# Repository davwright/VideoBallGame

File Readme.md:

# Video Ball Game
A faithful reproduction of  May 1976 ["Video Ball Game"](https://archive.org/details/EA1976/EA%201976-05%20May/page/n39/mode/2up) by [Electronics Australia](https://en.wikipedia.org/wiki/Electronics_Australia) magazine.  
Thanks to the kind help of [Jon Stanley](https://www.electronixandmore.com/projects/pong/index.html), who also built this. John's [demo](https://vimeo.com/801468536).  

The files are [kicad](https://www.kicad.org/) schematics and PCB.

# Fixes
The [errata](https://archive.org/details/EA1976/EA%201976-07%20July/page/n125/mode/2up) in July 1976 on page 125 list a few corrections.
* IC 5 is incorrectly shown as NAND on the schematic. Jon also discovered this independently.
* 2 0.0047uF polystyrene.
* There is also an error in a the RF circuit, but we are not building that.
* The Quad NAND and NOR integrated circuits today have diffirent pin configurations than those in 1976. This means the circuit board as is cannot be used.

# Improvements
* The 2200uF Capacitor is replaced with a 0.33uF capacitor and a 7806 6V regulator, that converts the 9V battery down to a stable 6V.
* 0.1uF decoupling capacitors are added to the VCC pins.
* pin headers are made for all switches and connectors so that they are all on one side of the board.
* ground and probe pins are added across the circuit for debugging.
* the board is printed double-sided, with a ground back plate, and removing the need for any jumper wires.
* the RF tuner circuit is completely removed, and the video signal is directly fed to composite video.
* Replaced IC5 with NOR. it is incorrectly NAND on schematic. This changes a lot.

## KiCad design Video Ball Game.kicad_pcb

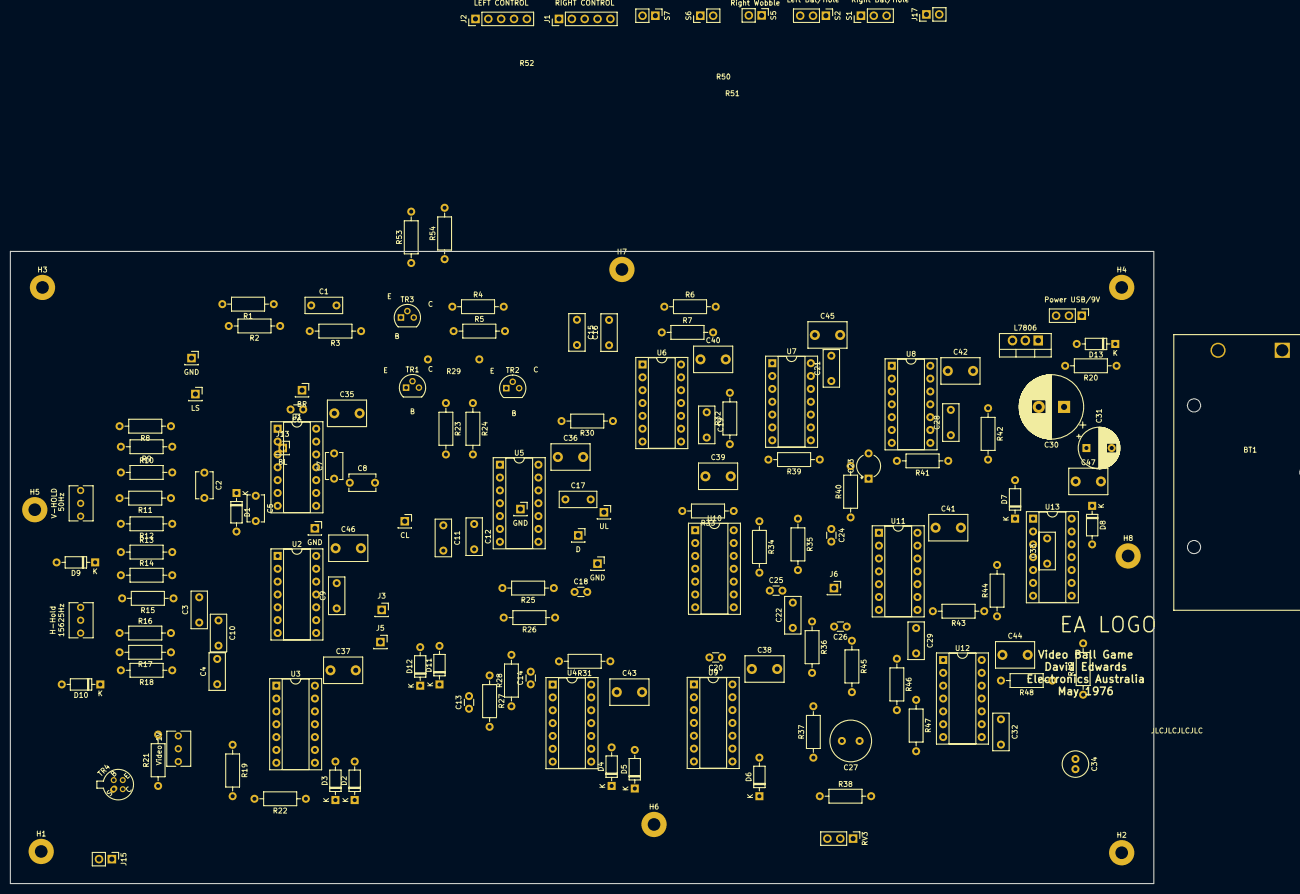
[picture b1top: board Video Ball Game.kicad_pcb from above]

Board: 2 copper layers, 226.1 x 125.0 mm, 168 parts (1 on the bottom side), 112 nets, no tracks yet.

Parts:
BT1: 9V; BatteryHolder_Eagle_12BH611-GR
C1, C3, C4, C9, C10, C19, C21, C28, C29, C32: 10nF red; C_Rect_L7.2mm_W3.0mm_P5.00mm_FKS2_FKP2_MKS2_MKP2
C2, C5, C7, C8: 330pF blue; C_Disc_D5.1mm_W3.2mm_P5.00mm
C6, C13, C14, C18, C24: 100pF blue; C_Disc_D3.0mm_W1.6mm_P2.50mm
C11, C12: 4.7nF red; C_Rect_L7.2mm_W3.0mm_P5.00mm_FKS2_FKP2_MKS2_MKP2
C15, C16, C33: 100nF red; C_Rect_L7.2mm_W3.0mm_P5.00mm_FKS2_FKP2_MKS2_MKP2
C17, C22: 33nF red; C_Rect_L7.2mm_W3.0mm_P5.00mm_FKS2_FKP2_MKS2_MKP2
C20: 220pF blue; C_Disc_D3.0mm_W1.6mm_P2.50mm
C23: 1uF TANTALUM; CP_Radial_Tantal_D4.5mm_P5.00mm
C25, C26: 330pF blue; C_Disc_D3.0mm_W1.6mm_P2.50mm
C27: 220uF elec 16VW 8x11 mm P 3.5; C_Radial_D8.0mm_H11.5mm_P3.50mm
C30: 2200uF elec; CP_Radial_D12.5mm_P5.00mm
C31: 22uF elec 16VW; CP_Radial_D8.0mm_P5.00mm
C34: 47uF elec 16VW radial 5x11mm P2.0; C_Radial_D5.0mm_H11.0mm_P2.00mm
C35, C36, C37, C38, C39, C40, C41, C42, C43, C44, C45, C46, C47: 100nF bypass red; C_Disc_D7.5mm_W5.0mm_P5.00mm
D1, D2, D3, D4, D5, D6, D7, D8, D9, D10, D11, D12, D13: 1N4148; D_DO-35_SOD27_P7.62mm_Horizontal
H1, H2, H3, H4, H5, H6, H7, H8: MountingHole; MountingHole_2.5mm_Pad
J1: RIGHT CONTROL; PinHeader_1x05_P2.54mm_Vertical
J2: LEFT CONTROL; PinHeader_1x05_P2.54mm_Vertical
J3: FS; PinSocket_1x01_P2.54mm_Vertical
J4: UL; PinSocket_1x01_P2.54mm_Vertical
J5: NH; PinSocket_1x01_P2.54mm_Vertical
J6: LL; PinSocket_1x01_P2.54mm_Vertical
J7, J9, J10, J11: GND; PinSocket_1x01_P2.54mm_Vertical
J8: LS; PinSocket_1x01_P2.54mm_Vertical
J12: D; PinSocket_1x01_P2.54mm_Vertical
J13: BL; PinSocket_1x01_P2.54mm_Vertical
J14: CL; PinSocket_1x01_P2.54mm_Vertical
J15: Video; PinHeader_1x02_P2.54mm_Vertical
J16: BR; PinSocket_1x01_P2.54mm_Vertical
J17: USB_B_Micro; PinHeader_1x02_P2.54mm_Vertical
R1: 390k; R_Axial_DIN0207_L6.3mm_D2.5mm_P10.16mm_Horizontal
R2, R14, R27, R28, R31: 22k; R_Axial_DIN0207_L6.3mm_D2.5mm_P10.16mm_Horizontal
R3: 2.2k; R_Axial_DIN0207_L6.3mm_D2.5mm_P10.16mm_Horizontal
R4, R5, R6, R7, R42, R46, R47: 470k; R_Axial_DIN0207_L6.3mm_D2.5mm_P10.16mm_Horizontal
R8, R9, R19, R21, R33, R34, R35, R40, R49, R53, R54: 10k; R_Axial_DIN0207_L6.3mm_D2.5mm_P10.16mm_Horizontal
R10, R11, R15: 33k; R_Axial_DIN0207_L6.3mm_D2.5mm_P10.16mm_Horizontal
R12: 56k; R_Axial_DIN0207_L6.3mm_D2.5mm_P10.16mm_Horizontal
R13, R23, R24, R32, R43: 47k; R_Axial_DIN0207_L6.3mm_D2.5mm_P10.16mm_Horizontal
R16: 330k; R_Axial_DIN0207_L6.3mm_D2.5mm_P10.16mm_Horizontal
R17: 1.2M; R_Axial_DIN0207_L6.3mm_D2.5mm_P10.16mm_Horizontal
R18, R36: 220k; R_Axial_DIN0207_L6.3mm_D2.5mm_P10.16mm_Horizontal
R20, R22, R37: 1k; R_Axial_DIN0207_L6.3mm_D2.5mm_P10.16mm_Horizontal
R25, R26, R29, R30, R44, R48: 10M; R_Axial_DIN0207_L6.3mm_D2.5mm_P10.16mm_Horizontal
R38: 3.3k; R_Axial_DIN0207_L6.3mm_D2.5mm_P10.16mm_Horizontal
R39, R41: 150k; R_Axial_DIN0207_L6.3mm_D2.5mm_P10.16mm_Horizontal
R45: 2.2M; R_Axial_DIN0207_L6.3mm_D2.5mm_P10.16mm_Horizontal
R50, R51: 22k; no pads
R52: 10k; no pads
RV1, RV2, RV4: 4.7k; Potentiometer_Bourns_3266Y_Vertical
RV3: 100k linear speed; PinHeader_1x03_P2.54mm_Vertical
S1: Right Bat/Hole; PinHeader_1x03_P2.54mm_Vertical
S2: Left Bat/Hole; PinHeader_1x03_P2.54mm_Vertical
S3: Power USB/9V; PinHeader_1x03_P2.54mm_Vertical
S5: Right Wobble; PinHeader_1x02_P2.54mm_Vertical
S6: Left Wobble; PinHeader_1x02_P2.54mm_Vertical
S7: Interaction; PinHeader_1x02_P2.54mm_Vertical
TR1, TR2: Q_NPN_BCE; TO-92
TR3: BC558; TO-92
TR4: Q_NPN_BCES; TO-72-4
U1, U2, U3, U4, U9, U10: 4011 QUAD NAND; DIP-14_W7.62mm_Socket
U5, U6, U7, U8, U11, U12, U13: 4001 QUAD NOR; DIP-14_W7.62mm_Socket
U14: L7806; TO-220-3_Vertical

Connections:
+6V: C31.1, C35.1, C36.1, C37.1, C38.1, C39.1, C40.1, C41.1, C42.1, C43.1, C44.1, C45.1, C46.1, C47.1, J1.4, J2.4, R8.1, R9.1, R19.1, R25.1, R26.1, R27.1, R28.1, R31.1, R33.1, R34.1, R35.1, R36.1, R53.2, R54.2, TR3.3 (E), U1.14 (VDD), U2.14 (VDD), U3.14 (VDD), U4.14 (VDD), U5.14 (VDD), U6.14 (VDD), U7.14 (VDD), U8.14 (VDD), U9.14 (VDD), U10.14 (VDD), U11.14 (VDD), U12.14 (VDD), U13.14 (VDD), U14.3 (OUT)
A: S1.2 (B), U4.2
B: S2.2 (B), U4.6
BL: C7.1, C14.2, J13.1, U1.5, U1.10, U9.1
BR: C6.1, C13.2, J16.1, U1.13, U3.3
BX: RV3.3, U5.10, U5.13
C: U4.9, U11.10, U13.5, U13.8
CL: C8.1, C18.2, J14.1, U1.8, U1.11, U9.2
D: U4.8, U11.11
E: U9.8, U9.9, U9.11
Earth: BT1.2 (-), C11.2, C12.2, C23.2, C26.1, C27.2, C30.2, C31.2, C34.2, C35.2, C36.2, C37.2, C38.2, C39.2, C40.2, C41.2, C42.2, C43.2, C44.2, C45.2, C46.2, C47.2, D13.2 (A), H1.1, H2.1, H3.1, H4.1, H5.1, H6.1, H7.1, H8.1, J1.1, J1.2, J2.1, J2.2, J7.1, J9.1, J10.1, J11.1, J15.2, R1.2, R2.2, R39.2, R40.2, R41.2, R43.2, RV1.3, RV2.3, RV4.3, TR4.3 (E), TR4.4 (S), U1.7 (VSS), U2.7 (VSS), U3.7 (VSS), U4.7 (VSS), U5.7 (VSS), U6.7 (VSS), U7.7 (VSS), U8.7 (VSS), U9.7 (VSS), U10.7 (VSS), U11.7 (VSS), U12.7 (VSS), U13.7 (VSS), U14.2 (GND)
F: R23.2, U5.4, U5.8
FS: C4.1, D10.1 (K), J3.1, U2.4, U2.13, U3.6
G: J1.3, J2.3, R53.1, U5.5
J: R24.2, U5.3, U5.12
LL: C3.1, C22.1, J6.1, U2.2, U2.11, U13.6
LS: C2.1, D9.1 (K), J8.1, U1.3, U3.2, U3.5
NH: C10.1, C17.1, J5.1, U2.3, U2.8, U6.8
unnamed: BT1.1 (+), S3.1
unnamed: C1.1, D10.2 (A), R2.1, R3.2, R4.1, R5.1, R46.1
unnamed: C1.2, R1.1, TR3.2 (B)
unnamed: C2.2, R11.1, U1.6
unnamed: C3.2, R15.1, U2.6
unnamed: C4.2, R16.1, U2.9
unnamed: C5.1, D1.1 (K), U1.2, U1.4
unnamed: C5.2, R12.1, U1.9
unnamed: C6.2, R10.1, U1.1
unnamed: C7.2, D1.2 (A), R13.1, U1.12
unnamed: C8.2, R14.1, U3.1
unnamed: C9.2, R17.1, U2.1
unnamed: C10.2, R18.1, U2.12
unnamed: C11.1, D12.2 (A), R25.2, U5.1
unnamed: C12.1, D11.2 (A), R26.2, U5.6
unnamed: C13.1, R27.2, U4.5
unnamed: C14.1, R28.2, U4.1
unnamed: C15.1, J2.5, R6.2, S6.1 (A)
unnamed: C15.2, R30.1, U6.5, U6.6
unnamed: C16.1, R29.2, U6.1, U6.2
unnamed: C16.2, J1.5, R7.2, S5.1 (A), S7.2 (B)
unnamed: C17.2, R33.2, U10.1, U10.13
unnamed: C18.1, R31.2, U4.12
unnamed: C19.1, U4.13, U6.11
unnamed: C19.2, R32.1, U6.9
unnamed: C20.1, R34.2, U10.8
unnamed: C20.2, U9.3, U9.5, U9.6
unnamed: C21.1, R39.1, U7.8, U7.9
unnamed: C21.2, U7.3
unnamed: C22.2, R35.2, U10.12
unnamed: C23.1, R42.2, R44.2, TR1.3 (E), TR2.3 (E)
unnamed: C24.1, R40.1, U11.12, U11.13
unnamed: C24.2, U11.3
unnamed: C25.1, C26.2, R36.2, R37.2
unnamed: C25.2, R45.1, U11.5, U11.6
unnamed: C27.1, R38.1, R45.2
unnamed: C28.1, R41.1, U8.8, U8.9
unnamed: C28.2, U8.3
unnamed: C29.1, R43.1, U11.8, U11.9
unnamed: C29.2, U12.3
unnamed: C30.1, R20.2, S3.2, U14.1 (IN)
unnamed: C32.1, R47.2, U12.10
unnamed: C32.2, R44.1, U12.8, U12.9
unnamed: C33.1, R48.2, U12.12, U12.13
unnamed: C33.2, U13.11
unnamed: D2.1 (K), D3.1 (K), D4.1 (K), D5.1 (K), D6.1 (K), R22.1
unnamed: D2.2 (A), U3.12, U4.3
unnamed: D3.2 (A), U3.8, U4.4
unnamed: D4.2 (A), U4.11
unnamed: D5.2 (A), U3.9, U3.13, U4.10
unnamed: D6.2 (A), U9.10
unnamed: D7.1 (K), U13.3
unnamed: D7.2 (A), D8.1 (K), R42.1
unnamed: D8.2 (A), U13.10
unnamed: D9.2 (A), R37.1
unnamed: D11.1 (K), U3.11
unnamed: D12.1 (K), U3.10
unnamed: D13.1 (K), R20.1
unnamed: J12.1, U5.9, U5.11
unnamed: R3.1, TR3.1 (C)
unnamed: R4.2, R6.1, U8.5, U8.6
unnamed: R5.2, R7.1, U7.5, U7.6
unnamed: R8.2, RV2.1
unnamed: R9.2, RV1.1
unnamed: R10.2, R11.2, R12.2, R13.2, R14.2, RV2.2
unnamed: R15.2, R16.2, R17.2, R18.2, RV1.2
unnamed: R21.1, TR4.1 (B)
unnamed: R21.2, U3.4
unnamed: R23.1, TR1.1 (B)
unnamed: R24.1, TR2.1 (B)
unnamed: R29.1, TR1.2 (C), U6.3
unnamed: R30.2, TR2.2 (C), U6.4
unnamed: R32.2, U6.10, U6.12, U6.13
unnamed: R38.2, RV3.1, RV3.2
unnamed: R46.2, R47.1, U12.5, U12.6
unnamed: R48.1, R49.1, U12.11, U13.12, U13.13
unnamed: C34.1, R49.2
unnamed: S1.1 (A), U7.10, U7.12, U7.13
unnamed: S1.3 (C), U7.11
unnamed: S2.1 (A), U8.10, U8.12, U8.13
unnamed: S2.3 (C), U8.11
unnamed: J17.1 (VBUS), S3.3
unnamed: U7.1, U7.2, U7.4
unnamed: U8.1, U8.2, U8.4
unnamed: U10.3, U10.5, U10.6
unnamed: U10.4, U13.9
unnamed: U9.4, U10.9
unnamed: U9.13, U10.10
unnamed: U9.12, U10.11
unnamed: U11.1, U11.2, U11.4
unnamed: U12.1, U12.2, U12.4
unnamed: U13.1, U13.2, U13.4
UL: C9.1, J4.1, U2.5, U2.10, U10.2
VIDEO: J15.1, R19.2, R22.2, RV4.2, TR4.2 (C)

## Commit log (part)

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2023-03-04 jon's changes
2023-03-05 fixed all footprints - pcb need retracing.
2023-03-29 USB power. removed all traces for retracing.
2025-04-17 updated to Kicad 9.0
2025-04-17 replaced PP with ceramic for decoupling caps
